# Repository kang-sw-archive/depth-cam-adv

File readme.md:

# Advanced Depth Map Generation System

## Major goals
1. Superpixel과 spectral clustering에 기반한 image segmentation 수행
2. 각 image segment에서 목표 샘플 위치 배열 추출
3. 목표 샘플 위치를 깊이 측정 장비에 전달
4. 3으로부터 얻은 깊이 샘플로 전체 깊이 데이터 추정

## Milestones
1. Matlab의 Image segmentation 코드 OpenCV로 migrate
2. 기존 펌웨어(범위 스캔)를 태스크 큐 파싱하여 스케쥴에 따라 캡쳐하는 방식으로 업그레이드
3. 라즈베리 파이에 1에서 OpenCV로 구현한 프로그램 최적화
4. PC에서 TCP/IP 프로토콜을 통해 장비 제어하는 콘솔 라이브러리 작성 (dll 형태)
5. Raspberry Pi에서 로컬 IP로 접근 시 HTTPS/HTTP 프로토콜로 장비 상태 리포트 웹페이지 전송

## Structure

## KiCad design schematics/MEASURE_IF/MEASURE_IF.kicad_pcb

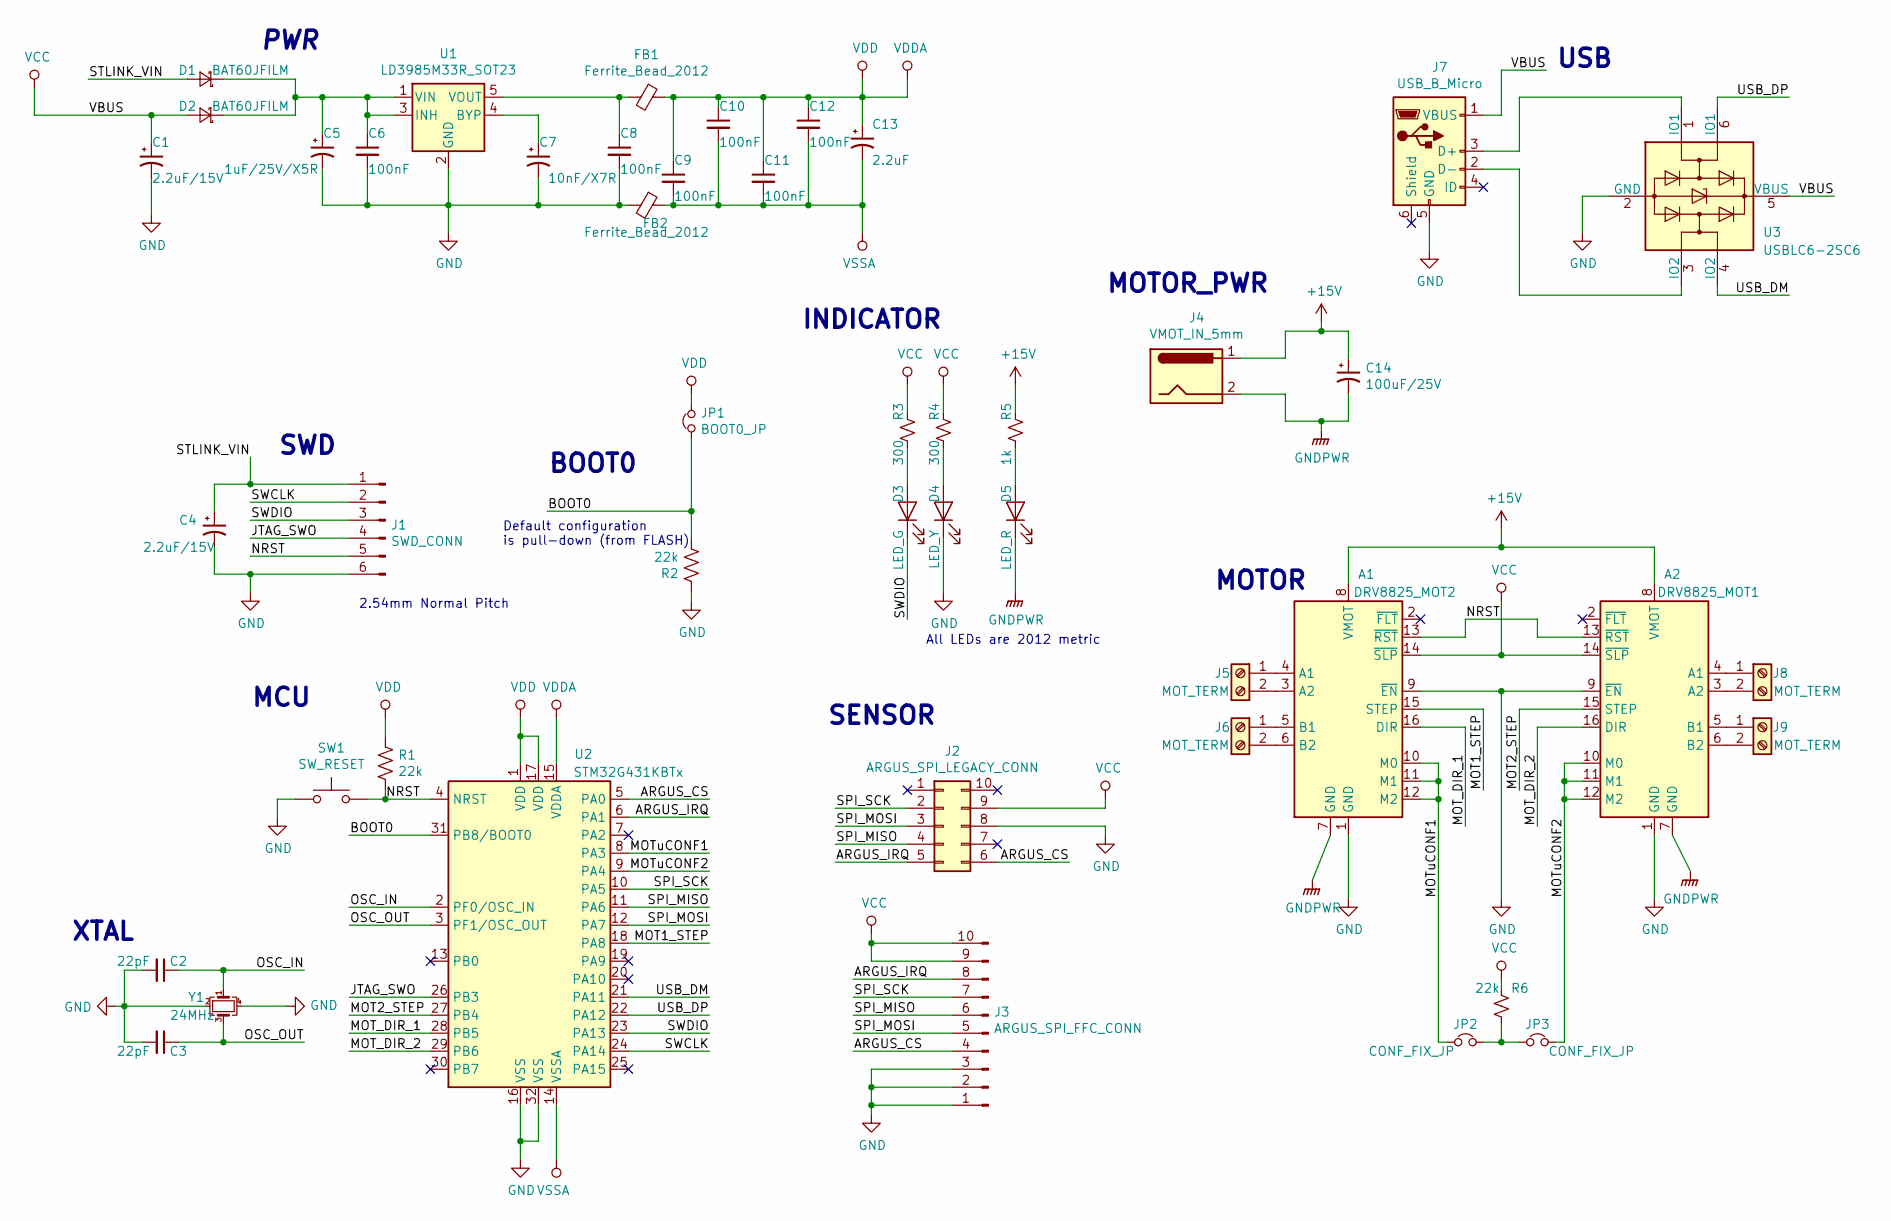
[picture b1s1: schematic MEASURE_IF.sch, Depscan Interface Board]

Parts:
A1: DRV8825_MOT2; Pololu_Breakout-16_15.2x20.3mm
A2: DRV8825_MOT1; Pololu_Breakout-16_15.2x20.3mm
C1, C4: 2.2uF/15V; C_0805_2012Metric_Pad1.15x1.40mm_HandSolder
C2, C3: 22pF; C_0805_2012Metric_Pad1.15x1.40mm_HandSolder
C5: 1uF/25V/X5R; C_0805_2012Metric_Pad1.15x1.40mm_HandSolder
C6, C8, C9, C10, C11, C12: 100nF; C_0805_2012Metric_Pad1.15x1.40mm_HandSolder
C7: 10nF/X7R; C_0805_2012Metric_Pad1.15x1.40mm_HandSolder
C13: 2.2uF; C_0805_2012Metric_Pad1.15x1.40mm_HandSolder
C14: 100uF/25V; CP_Elec_6.3x5.2
D1, D2: BAT60JFILM; D_SOD-323
D3: LED_G; LED_0805_2012Metric
D4: LED_Y; LED_0805_2012Metric
D5: LED_R; LED_0805_2012Metric
FB1, FB2: Ferrite_Bead_2012; L_0805_2012Metric_Pad1.15x1.40mm_HandSolder
J1: SWD_CONN; PinHeader_2x03_P2.54mm_Vertical
J2: ARGUS_SPI_LEGACY_CONN; CONN02x05CLOCKWISE
J3: ARGUS_SPI_FFC_CONN; Hirose_FH12-10S-0.5SH_1x10-1MP_P0.50mm_Horizontal
J4: VMOT_IN_5mm; BarrelJack_Horizontal
J5, J6, J8, J9: MOT_TERM; TerminalBlock_bornier-2_P5.08mm
J7: USB_B_Micro; USB_Micro-B_Molex_47346-0001
JP1: BOOT0_JP; PinHeader_1x02_P2.54mm_Vertical
JP2, JP3: CONF_FIX_JP; SolderJumper-2_P1.3mm_Open_TrianglePad1.0x1.5mm
R1, R2, R6: 22k; R_0805_2012Metric_Pad1.15x1.40mm_HandSolder
R3, R4: 300; R_0805_2012Metric_Pad1.15x1.40mm_HandSolder
R5: 1k; R_0805_2012Metric_Pad1.15x1.40mm_HandSolder
SW1: SW_RESET; SW_SMD_TS1107
U1: LD3985M33R_SOT23; SOT-23-5
U2: STM32G431KBTx; LQFP-32_7x7mm_P0.8mm
U3: USBLC6-2SC6; SOT-23-6
Y1: 24MHz; Crystal_SMD_SeikoEpson_FA238V-4Pin_3.2x2.5mm_HandSoldering

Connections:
+15V: A1.8 (VMOT), A2.8 (VMOT), C14.1, J4.1, R5.1
/ARGUS_CS: J2.6, J3.4, U2.5 (PA0)
/ARGUS_IRQ: J2.5, J3.8, U2.6 (PA1)
/BOOT0: JP1.1, R2.2, U2.31 (PB8/BOOT0)
/JTAG_SWO: J1.4, U2.26 (PB3)
/MOT1_STEP: A1.15 (STEP), U2.18 (PA8)
/MOT2_STEP: A2.15 (STEP), U2.27 (PB4)
/MOT_DIR_1: A1.16 (DIR), U2.28 (PB5)
/MOT_DIR_2: A2.16 (DIR), U2.29 (PB6)
/MOTuCONF1: A1.10 (M0), A1.11 (M1), A1.12 (M2), JP2.1, U2.8 (PA3)
/MOTuCONF2: A2.10 (M0), A2.11 (M1), A2.12 (M2), JP3.2, U2.9 (PA4)
/NRST: A1.13 (~RST), A2.13 (~RST), J1.5, R1.2, SW1.2, U2.4 (NRST)
/OSC_IN: C2.1, U2.2 (PF0/OSC_IN), Y1.1
/OSC_OUT: C3.1, U2.3 (PF1/OSC_OUT), Y1.3
/SPI_MISO: J2.4, J3.6, U2.11 (PA6)
/SPI_MOSI: J2.3, J3.5, U2.12 (PA7)
/SPI_SCK: J2.2, J3.7, U2.10 (PA5)
/STLINK_VIN: C4.1, D1.2 (A), J1.1
/SWCLK: J1.2, U2.24 (PA14)
/SWDIO: D3.1 (K), J1.3, U2.23 (PA13)
/USB_DM: U2.21 (PA11), U3.4 (IO2)
/USB_DP: U2.22 (PA12), U3.6 (IO1)
GND: A1.1 (GND), A1.9 (~EN), A2.1 (GND), A2.9 (~EN), C1.2, C2.2, C3.2, C4.2, C5.2, C6.2, C7.2, C8.2, D4.1 (K), FB2.2, J1.6, J2.8, J3.1, J3.2, J3.3, J7.5 (GND), R2.1, SW1.1, U1.2 (GND), U2.16 (VSS), U2.32 (VSS), U3.2 (GND), Y1.2, Y1.4
GNDPWR: A1.7 (GND), A2.7 (GND), C14.2, D5.1 (K), J4.2
unnamed: A1.3 (A2), J5.2
unnamed: A1.4 (A1), J5.1
unnamed: A1.5 (B1), J6.1
unnamed: A1.6 (B2), J6.2
unnamed: A2.3 (A2), J8.2
unnamed: A2.4 (A1), J8.1
unnamed: A2.5 (B1), J9.1
unnamed: A2.6 (B2), J9.2
unnamed: C5.1, C6.1, D1.1 (K), D2.1 (K), U1.1 (VIN), U1.3 (INH)
unnamed: C7.1, U1.4 (BYP)
unnamed: C8.1, FB1.2, U1.5 (VOUT)
unnamed: D3.2 (A), R3.2
unnamed: D4.2 (A), R4.2
unnamed: D5.2 (A), R5.2
unnamed: J7.2 (D-), U3.3 (IO2)
unnamed: J7.3 (D+), U3.1 (IO1)
unnamed: JP2.2, JP3.1, R6.2
VCC: A1.14 (~SLP), A2.14 (~SLP), C1.1, D2.2 (A), J2.9, J3.9, J3.10, J7.1 (VBUS), R3.1, R4.1, R6.1, U3.5 (VBUS)
VDD: C9.1, C10.1, C11.1, C12.1, C13.1, FB1.1, JP1.2, R1.1, U2.1 (VDD), U2.15 (VDDA), U2.17 (VDD)
VSSA: C9.2, C10.2, C11.2, C12.2, C13.2, FB2.1, U2.14 (VSSA)

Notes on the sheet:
PWR
USB
MCU
MOTOR
SWD
XTAL
2.54mm Normal Pitch
SENSOR
MOTOR_PWR
INDICATOR
All LEDs are 2012 metric
BOOT0
Default configuration is pull-down (from FLASH)

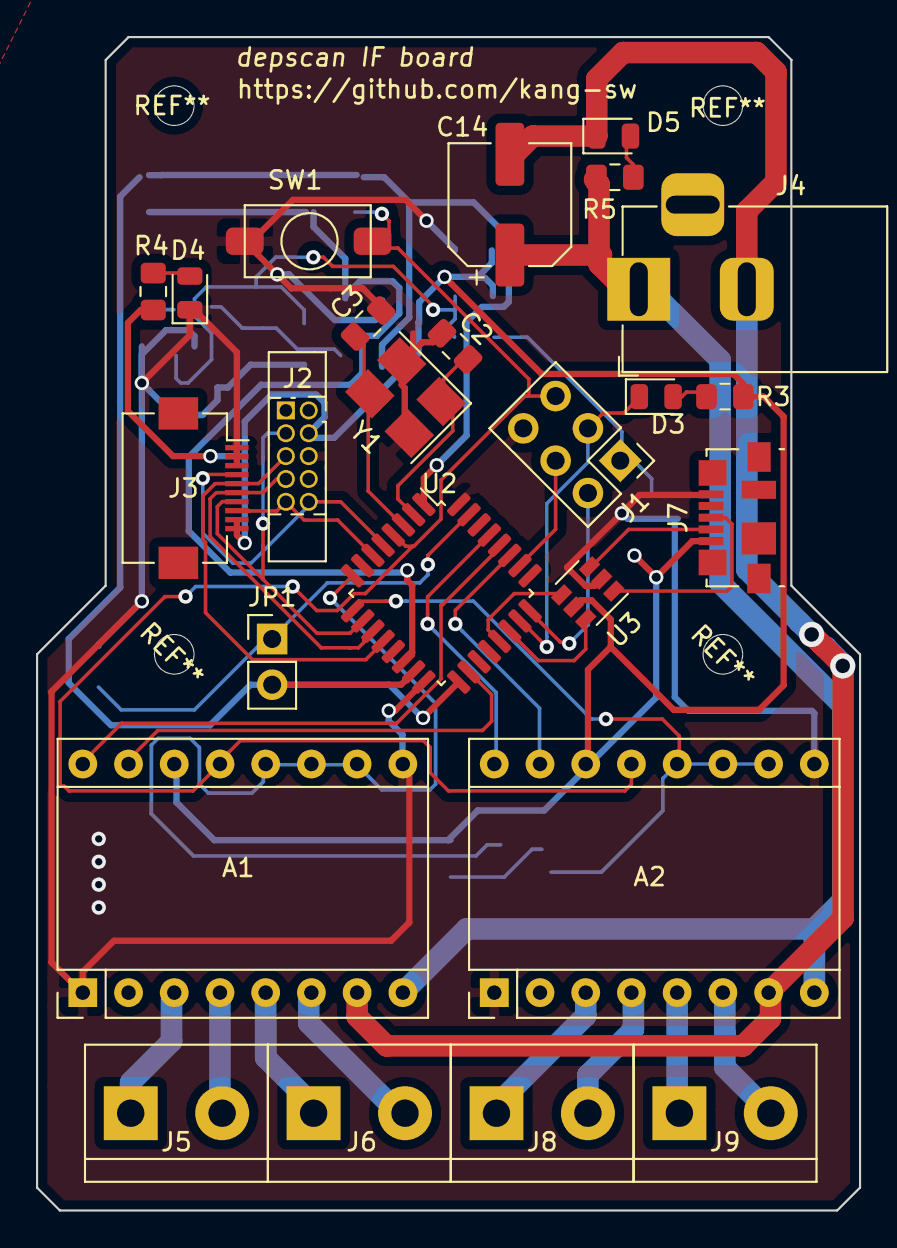
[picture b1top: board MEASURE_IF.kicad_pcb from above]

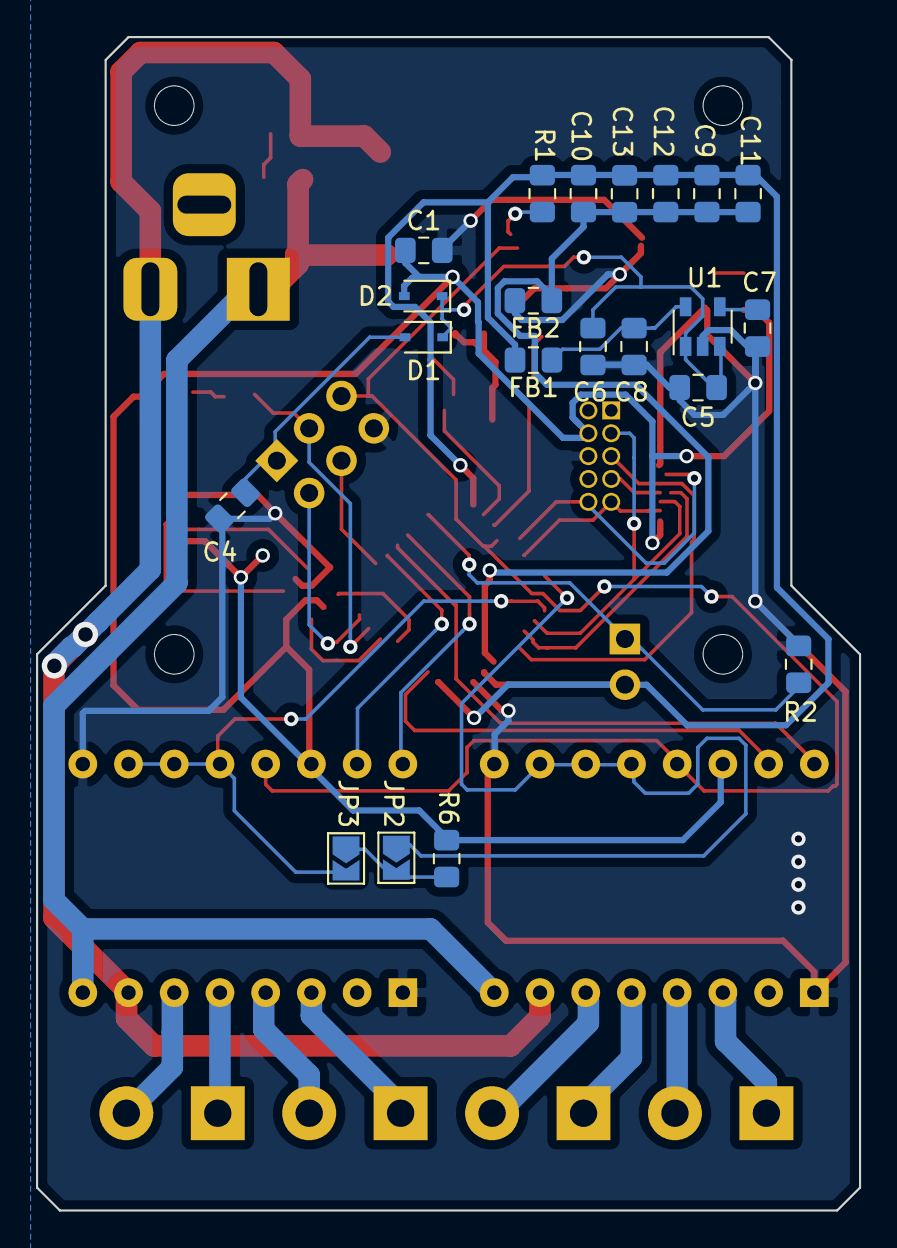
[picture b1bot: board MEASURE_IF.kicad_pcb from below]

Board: 2 copper layers, 45.7 x 65.2 mm, 46 parts (21 on the bottom side), 44 nets.

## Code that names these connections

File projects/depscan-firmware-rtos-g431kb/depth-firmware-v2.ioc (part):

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Mcu.Name=STM32G431K(6-8-B)Tx
Mcu.Package=LQFP32
Mcu.UserName=STM32G431KBTx
PA0.GPIOParameters=GPIO_Label
PA0.GPIO_Label=ARGUS_CS
PA0.Signal=GPIO_Output
PA1.GPIOParameters=GPIO_PuPd,GPIO_Label,GPIO_ModeDefaultEXTI
PA1.GPIO_Label=ARGUS_IRQ
PA1.GPIO_ModeDefaultEXTI=GPIO_MODE_IT_FALLING
PA1.GPIO_PuPd=GPIO_PULLUP
PA1.Signal=GPXTI1
PA11.Mode=Device
PA11.Signal=USB_DM
PA12.Mode=Device
PA12.Signal=USB_DP
PA13.GPIOParameters=GPIO_Label
PA13.GPIO_Label=T_SWDIO
PA13.Mode=Serial_Wire
PA13.Signal=SYS_JTMS-SWDIO
PA14.GPIOParameters=GPIO_Label
PA14.GPIO_Label=T_SWCLK
PA14.Mode=Serial_Wire
PA14.Signal=SYS_JTCK-SWCLK
PA5.Mode=Full_Duplex_Master
PA5.Signal=SPI1_SCK
PA6.Mode=Full_Duplex_Master
PA6.Signal=SPI1_MISO
PA7.Mode=Full_Duplex_Master
PA7.Signal=SPI1_MOSI
PA8.GPIOParameters=GPIO_Label
PA8.GPIO_Label=MOT1_STEP
PA8.Signal=S_TIM1_CH1
PA9.GPIOParameters=GPIO_PuPd,GPIO_Label
PA9.GPIO_Label=USB_VBUS
PA9.GPIO_PuPd=GPIO_PULLDOWN
PA9.Signal=GPIO_Input
PB3.GPIOParameters=GPIO_Label
PB3.GPIO_Label=T_SWO
PB3.Signal=SYS_JTDO-SWO
PB4.GPIOParameters=GPIO_Label
PB4.GPIO_Label=MOT2_STEP
PB4.Signal=S_TIM3_CH1
PB5.GPIOParameters=GPIO_Label
PB5.GPIO_Label=MOT_DIR_1
PB5.Signal=GPIO_Output
PB6.GPIOParameters=GPIO_Label
PB6.GPIO_Label=MOT_DIR_2
PB6.Signal=GPIO_Output
PB8-BOOT0.GPIOParameters=GPIO_Label
PB8-BOOT0.GPIO_Label=LD2 [green]
PB8-BOOT0.Signal=GPIO_Output
PF0-OSC_IN.Mode=HSE-External-Oscillator
PF0-OSC_IN.Signal=RCC_OSC_IN
PF1-OSC_OUT.Mode=HSE-External-Oscillator
PF1-OSC_OUT.Signal=RCC_OSC_OUT
RCC.HSE_VALUE=24000000
RCC.SYSCLKFreq_VALUE=170000000
RCC.SYSCLKSource=RCC_SYSCLKSOURCE_PLLCLK
board=NUCLEO-G431KB
boardIOC=true

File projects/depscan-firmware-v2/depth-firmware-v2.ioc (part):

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Mcu.Name=STM32G431K(6-8-B)Tx
Mcu.Package=LQFP32
Mcu.UserName=STM32G431KBTx
PA1.GPIOParameters=GPIO_PuPd,GPIO_Label,GPIO_ModeDefaultEXTI
PA1.GPIO_Label=SPI_IRQ
PA1.GPIO_ModeDefaultEXTI=GPIO_MODE_IT_FALLING
PA1.GPIO_PuPd=GPIO_PULLUP
PA1.Signal=GPXTI1
PA11.Mode=Device
PA11.Signal=USB_DM
PA12.Mode=Device
PA12.Signal=USB_DP
PA13.GPIOParameters=GPIO_Label
PA13.GPIO_Label=T_SWDIO
PA13.Mode=Serial_Wire
PA13.Signal=SYS_JTMS-SWDIO
PA14.GPIOParameters=GPIO_Label
PA14.GPIO_Label=T_SWCLK
PA14.Mode=Serial_Wire
PA14.Signal=SYS_JTCK-SWCLK
PA2.GPIOParameters=GPIO_Label
PA2.GPIO_Label=USART2_TX [ST-LINKV3E_VCP_RX]
PA2.Mode=Asynchronous
PA2.Signal=USART2_TX
PA3.GPIOParameters=GPIO_Label
PA3.GPIO_Label=USART2_RX [ST-LINKV3E_VCP_TX]
PA3.Mode=Asynchronous
PA3.Signal=USART2_RX
PA4.Mode=NSS_Signal_Hard_Output
PA4.Signal=SPI1_NSS
PA5.Mode=Full_Duplex_Master
PA5.Signal=SPI1_SCK
PA6.Mode=Full_Duplex_Master
PA6.Signal=SPI1_MISO
PA7.Mode=Full_Duplex_Master
PA7.Signal=SPI1_MOSI
PA8.GPIOParameters=GPIO_Label
PA8.GPIO_Label=MOT1_STEP
PA8.Signal=S_TIM1_CH1
PB3.GPIOParameters=GPIO_Label
PB3.GPIO_Label=T_SWO
PB3.Signal=SYS_JTDO-SWO
PB4.GPIOParameters=GPIO_Label
PB4.GPIO_Label=MOT2_STEP
PB4.Signal=S_TIM3_CH1
PB8-BOOT0.GPIOParameters=GPIO_Label
PB8-BOOT0.GPIO_Label=LD2 [green]
PB8-BOOT0.Signal=GPIO_Output
PF0-OSC_IN.Mode=HSE-External-Oscillator
PF0-OSC_IN.Signal=RCC_OSC_IN
PF1-OSC_OUT.Mode=HSE-External-Oscillator
PF1-OSC_OUT.Signal=RCC_OSC_OUT
RCC.HSE_VALUE=24000000
RCC.SYSCLKFreq_VALUE=170000000
RCC.SYSCLKSource=RCC_SYSCLKSOURCE_PLLCLK
board=NUCLEO-G431KB
boardIOC=true

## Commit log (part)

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2020-01-22 New initial commit
2020-01-22 Rename obsolete projest
2020-01-22 Add new docs/refs
2020-01-22 Configure Makefile project for visual studio
2020-01-23 Configure build environment
2020-01-23 Test configure new makefile project
2020-01-23 Configure Intellisense
2020-01-23 Configure cross-platform build for VS
    + Now visual studio's debug interface can be used to debug STM project
2020-01-24 Configure VS debug
2020-01-24 Configure RTOS
2020-01-24 Configure debug process for vs
    Required programsf for vs debug:
    - Embedded arm dev sdk for vs
    - arm-none-eabi-gnu
    - openocd
    - netcat
    And these files should be established.
2020-01-25 Add new reference: FreeRTOS
2020-01-26 Improt new submodule: EASTL
2020-01-26 Unload sumboudle; EASTL
2020-01-26 Configure C++ build
2020-01-27 Regenerate msp
    + SPI
    + GPIOs
2020-01-27 Reorganize source tree
2020-01-27 Set default host transceiver as USB CDC
2020-01-27 Simplify IRQ handler for TIM1, TIM3
2020-01-27 Comment outline for init process
2020-01-27 Add os dimension helper macro
2020-01-27 Apply submodule change
2020-01-27 Implement outline to call host IO procedure
2020-01-27 Add hardware functionality
2020-01-27 Implement primal echo program
    Implement USB CDC RW impl layer
    Reorganize source tree
    Set default host transceiver as USB CDC
    Simplify IRQ handler for TIM1, TIM3
    Comment outline for init process
    Add os dimension helper macro
2020-01-27 Reconfigure project
2020-01-27 Regenerate MSP
    ~ Some NVIC priorities were modified.
2020-01-27 Rollback malloc() free() rebinds
2020-01-27 Regenerate code to resolve hard fault error
2020-01-27 Resolve Hard fault error
    - EXTI IRQ1 is disabled. Seems not correctly configured.
    - Default task will sustain forever. Taskexit() from default task causes
    trouble.
2020-01-27 Verify primal echo program through USB
2020-01-27 Apply renaming of transceiver
2020-01-27 Add outline for logger
    This class is wrapper of gHostConnection transceiver.
2020-01-28 Add protocol headers
2020-01-28 Update usb-api
2020-01-28 Remove CmdProc associated declarations
2020-01-28 Implement host data receive logic
2020-01-28 Implement command procedure frame
2020-01-28 Implement host transfer frame
2020-01-28 Implement basic IOs to host
2020-01-28 Regenrate MSP; Adjust heap size
2020-01-28 Implement flush to host
2020-01-28 Update .clang-format
2020-01-28 Update format
2020-01-28 Verify Host IO operation
    + Add command-line procedure for scangui
    - Fix invalid string token parser operation
2020-01-28 Define new logging functions
2020-01-28 Add binary handler symbol
    . For future implementation ...
2020-01-30 Fix typo
2020-01-30 Regenerate code; Let tim2 have more accuracy
2020-01-30 Improve console-app operation
2020-01-30 Implement GetTime() logic for global
2020-01-30 Implement HW timer logic
2020-01-30 Verify hardware timer
2020-01-30 Add SetTimer API for IRQ
2020-01-31 Import ARGUS library
2020-01-31 Improve timer operation
2020-01-31 [wip] Implementation of ARGUS HAL functions
2020-01-31 Implement ARGUS HAL functions
    - Yet S2PI operation not verified.
2020-01-31 [wip] Implementation of capture command handler
2020-01-31 Reapply clang-format
2020-01-31 Rename 'arch' directory into 'platform'
2020-01-31 Correct include changes
2020-01-31 Veryfied synchronous SPI operation
    - However, for asynchronous SPI data transfer using a DMA controller,
    the read buffer is pulled by one byte.
2020-01-31 Discard asynchronous SPI using DMA
    - The 'Byte Shift' problem, which occurs when using the DMA feature, has
    not been fixed. It has been reported from several communities that this
    is a hardware defect, so the inherent resolution seems difficult. In
    case of using synchronous SPI, it works without any defect, so it is not
    a big problem.
2020-01-31 Add motor interface functions
2020-01-31 Add doxygen comments
2020-01-31 Fix some comments
2020-02-01 Reflow comments
2020-02-01 Detach test section
2020-02-01 Create interface for sensor and motor
2020-02-01 Create distance sensor impl file
2020-02-01 Apply new format
2020-02-01 Apply submodule changes
2020-02-01 Apply column width 80
2020-02-01 Rename logger functions into Msg, Msgf
2020-02-01 Change format a bit
2020-02-01 Implement sensor handling functionalities
2020-02-01 Change comment format
2020-02-01 Implement distance sensor condition checker
    + Block configuration during capture
2020-02-01 Arrange code outline
    + Extract functions from procedure
2020-02-01 [wip] Fix error on timer logic
2020-02-01 [wip] Still stick with hard-fault ...
    - Seems error occurs when TransferFrame called
    thru IRQ callback, but hard to know exact error
    since there's no information about tasks.
2020-02-01 Add eclipse project configurations
2020-02-01 Fix hard fault error on measurement
    - The biggest cause of all errors came from ridiculous mistakes. No
    validation was done during the invoke of the measurement callback, which
    caused a segmentation fault.
    - Another error is due to the incomplete implementation of the vsnprintf
    function in the nano spec, which causes miscalculated characters to
    contaminate the stack, making it difficult to track.
2020-02-02 Fix timer fault
    - by resolving fslist's invalid operation ...
    ~ Update TODOs, BUGs
2020-02-02 Regroup interfaces
2020-02-02 Implement motor IRQ handler's outline
    + Lower down motor timer IRQ priority to 5 to use
    FreeRTOS APIs inside of motor ISR.
2020-02-02 Implement arch-independent logics to drive motor
    ~ Because this implementation takes full advantage of FPU, precise
    performance analysis must be preceded for any potential loss of
    performance.
2020-02-03 Implement motor driver's hardware side
2020-02-03 Add motor initialization code
    + Mandate argument error handling to each handler.
2020-02-03 Implement motor logical test
2020-02-03 Make apndToHostBuf ISR compatible
2020-02-03 Change default acceleration value to 500k
2020-02-03 Rename directory
2020-02-03 Implement Depscan Interface Board
2020-02-05 Implement IF board artwork:
2020-02-06 Fix pin location error
2020-02-06 Reduce dependency on chip specific headers
2020-02-07 Circuit minor update
2020-02-07 Reduce .bss usage
2020-02-07 Fix issue that acceleration value is not applied
    - Simply fixed by adjusting evaluation priority
    + Found ideal default accel/velocity value
2020-02-07 Fix comment
2020-02-07 Make capturer instance be in sync with device
2020-02-07 Apply revised protocol commands
2020-02-07 Implement report, help command
2020-02-07 Resolve c++17 compilation issue
2020-02-07 Remove unused static declerations
2020-02-07 Apply c++17 build environment
2020-02-07 Rename macro more intuitive
2020-02-07 Implement configurations
2020-02-07 Size optimization
2020-02-07 Resolve link error
2020-02-08 Don't use stack memory in log functions
    + This will help to reduce stack memory usage, thus stack memory allocation
    for each task can be shrink.
2020-02-08 Apply simple assertion logic
2020-02-08 Resolve disconnection issue
    + Disconnection issue was resolved by deallocating com stream before
    open new com stream.
    + Now the connection process is more polished.
2020-02-08 [WIP] Add a watchdog timer to measurement
    + It is a timer instance that has a longer delay than measurement time.
    If the measurement succeeds before it triggers, it'll be aborted
    automatically. However when if it triggers, it is treated as an error
    that something is lost during measurement.
2020-02-08 [WIP] Handling error on async measurement
2020-02-08 Comment TODOs
2020-02-09 Set default configuration on sensor init proc
2020-02-09 Fix segfault on disconnection
2020-02-09 Fix invalid watchdog timer trigger issue
    - The major issue was resolved by correcting timer logic's invalid
    find() operation
2020-02-09 Add new debug-only logger
2020-02-10 Move page documentation into source file
2020-02-10 Change measurement callback error handling method
    + Now non-zero evaluation result is not treated as error, but still
    should be treated carefully. Error code handling now will be mandated
    to the callee.
2020-02-10 Use returned measured data with non-zero error code
2020-02-10 Add new aliases for priority constant
2020-02-10 Modify scanner communication data protocol
    + Now each transfer request will have its own 16-bit ID. Therefore each
    point capture request is treated independently for each other.
2020-02-10 Refactor DistSens_MeasureSync
    + Now this function returns actual error code from ARGUS library
2020-02-10 Suppress warnings by correcting them
2020-02-10 Use correct return value to fit in type
2020-02-10 Implement scanning task
    + A scan job consists of a set of asynchronous jobs. To maintain the st
    ability of the device state, state changes such as stops and pauses are
    always performed when all asynchronous tasks have finished.
2020-02-11 Modify initial motor clock speed
2020-02-11 Re-factor motor position logics
    + Motor APIs to control motor position value is clarified.
    - Removed ResetPos
2020-02-11 Clarify command type alias' size
    + Now 'auto' keyword can be used with command type
2020-02-11 Remove local-able data members
2020-02-11 Improve retry logic for scanning process
    + Now the device will reinitialize sensor for every measurement failure
2020-02-11 Invert X motor direction
2020-02-11 Fix incorrect parameter settings
2020-02-11 Comment for a bug
2020-02-11 Update to new device commands
2020-02-11 Fix segfault on reconnect for GUI app
2020-02-12 Add distance sensor test logic for console
2020-02-12 Fix invisible elapsed time
2020-02-13 Fix invalid connector boundary
2020-02-14 Fix motor position error
    + Error on motor position on fast motor movement was fixed by using
    timer PWM one pulse mode
2020-02-17 Change data communication method to ASCII
    + Originally data communication between the host and the device used
    specialized data descriptor with 4 bytes of size.
    However, this method prevents a user from using the device through a
    primitive terminal program. Instead, it forces us to use a special
    library that handles the protocol.
    Since the data transmission rate of the USB-FS interface is outstanding
2020-02-17 Configure OpenCV build env
2020-02-17 Configure SLIC with CUDA environement
2020-02-19 Verify accelerated SLIC operation
2020-02-19 Configure build environment for imseg
    -- Previous commits --
    Verify accelerated SLIC operation
    Configure SLIC with CUDA environement
    Configure OpenCV build env
2020-02-20 Port overall system to G431KB based board
    ~ VID, PID is changed to 0x6080, 0xccd2 respectedly
    - The build configuration for F401VC is now obsolete. Mamma mia!
    ---- PREVIOUS COMMITS ----
    Remove unused project directory
    - A separate project directory for G431KB is removed. From now on,
    both F401VC and G431KB projects will be managed at the same time and
2020-02-21 Make motor callback delay for 200us
    + Since finishing the PWM signal transfer does not mean the motor is
    actually stopped, 200 us of delay is added to the motor movement done
    callback call.
2020-02-23 Reorganize host library source code
    + Now API methods to search appropriate COM port has migrated to
    scanlib from scangui.
2020-02-24 Improve board artwork
2020-02-29 Improve outline of overall image processing
    + Improvement on device interface
    + New features with opencv manipulation
    + Improvement on scanlib APIs
    >>>>>> PRIVIOUS COMMITS
    [WIP] Resolving communication issue
    Implement center point calculation
2020-02-29 Rename function
2020-02-29 Fix exception on CreateFile
2020-02-29 Improve debugging information display
2020-03-01 Add samples
2020-03-01 Fix fatal error on device disconnection
2020-03-01 Treat stalled data as non-error data
2020-03-01 Improve debug image display
2020-04-01 Save dpta file automatically on every capture
2020-04-01 Generate few more samples
2020-04-01 Shows distance of given pixel
2020-04-01 Save filtered depth image as result
2020-04-01 Save both of filtered and raw image
2020-04-02 Fix incorrect camera initialization

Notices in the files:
schematics/MEASURE_IF/MEASURE_IF.kicad_pcb:
Copyright 2020. Seungwoo Kang. All rights reserved.
